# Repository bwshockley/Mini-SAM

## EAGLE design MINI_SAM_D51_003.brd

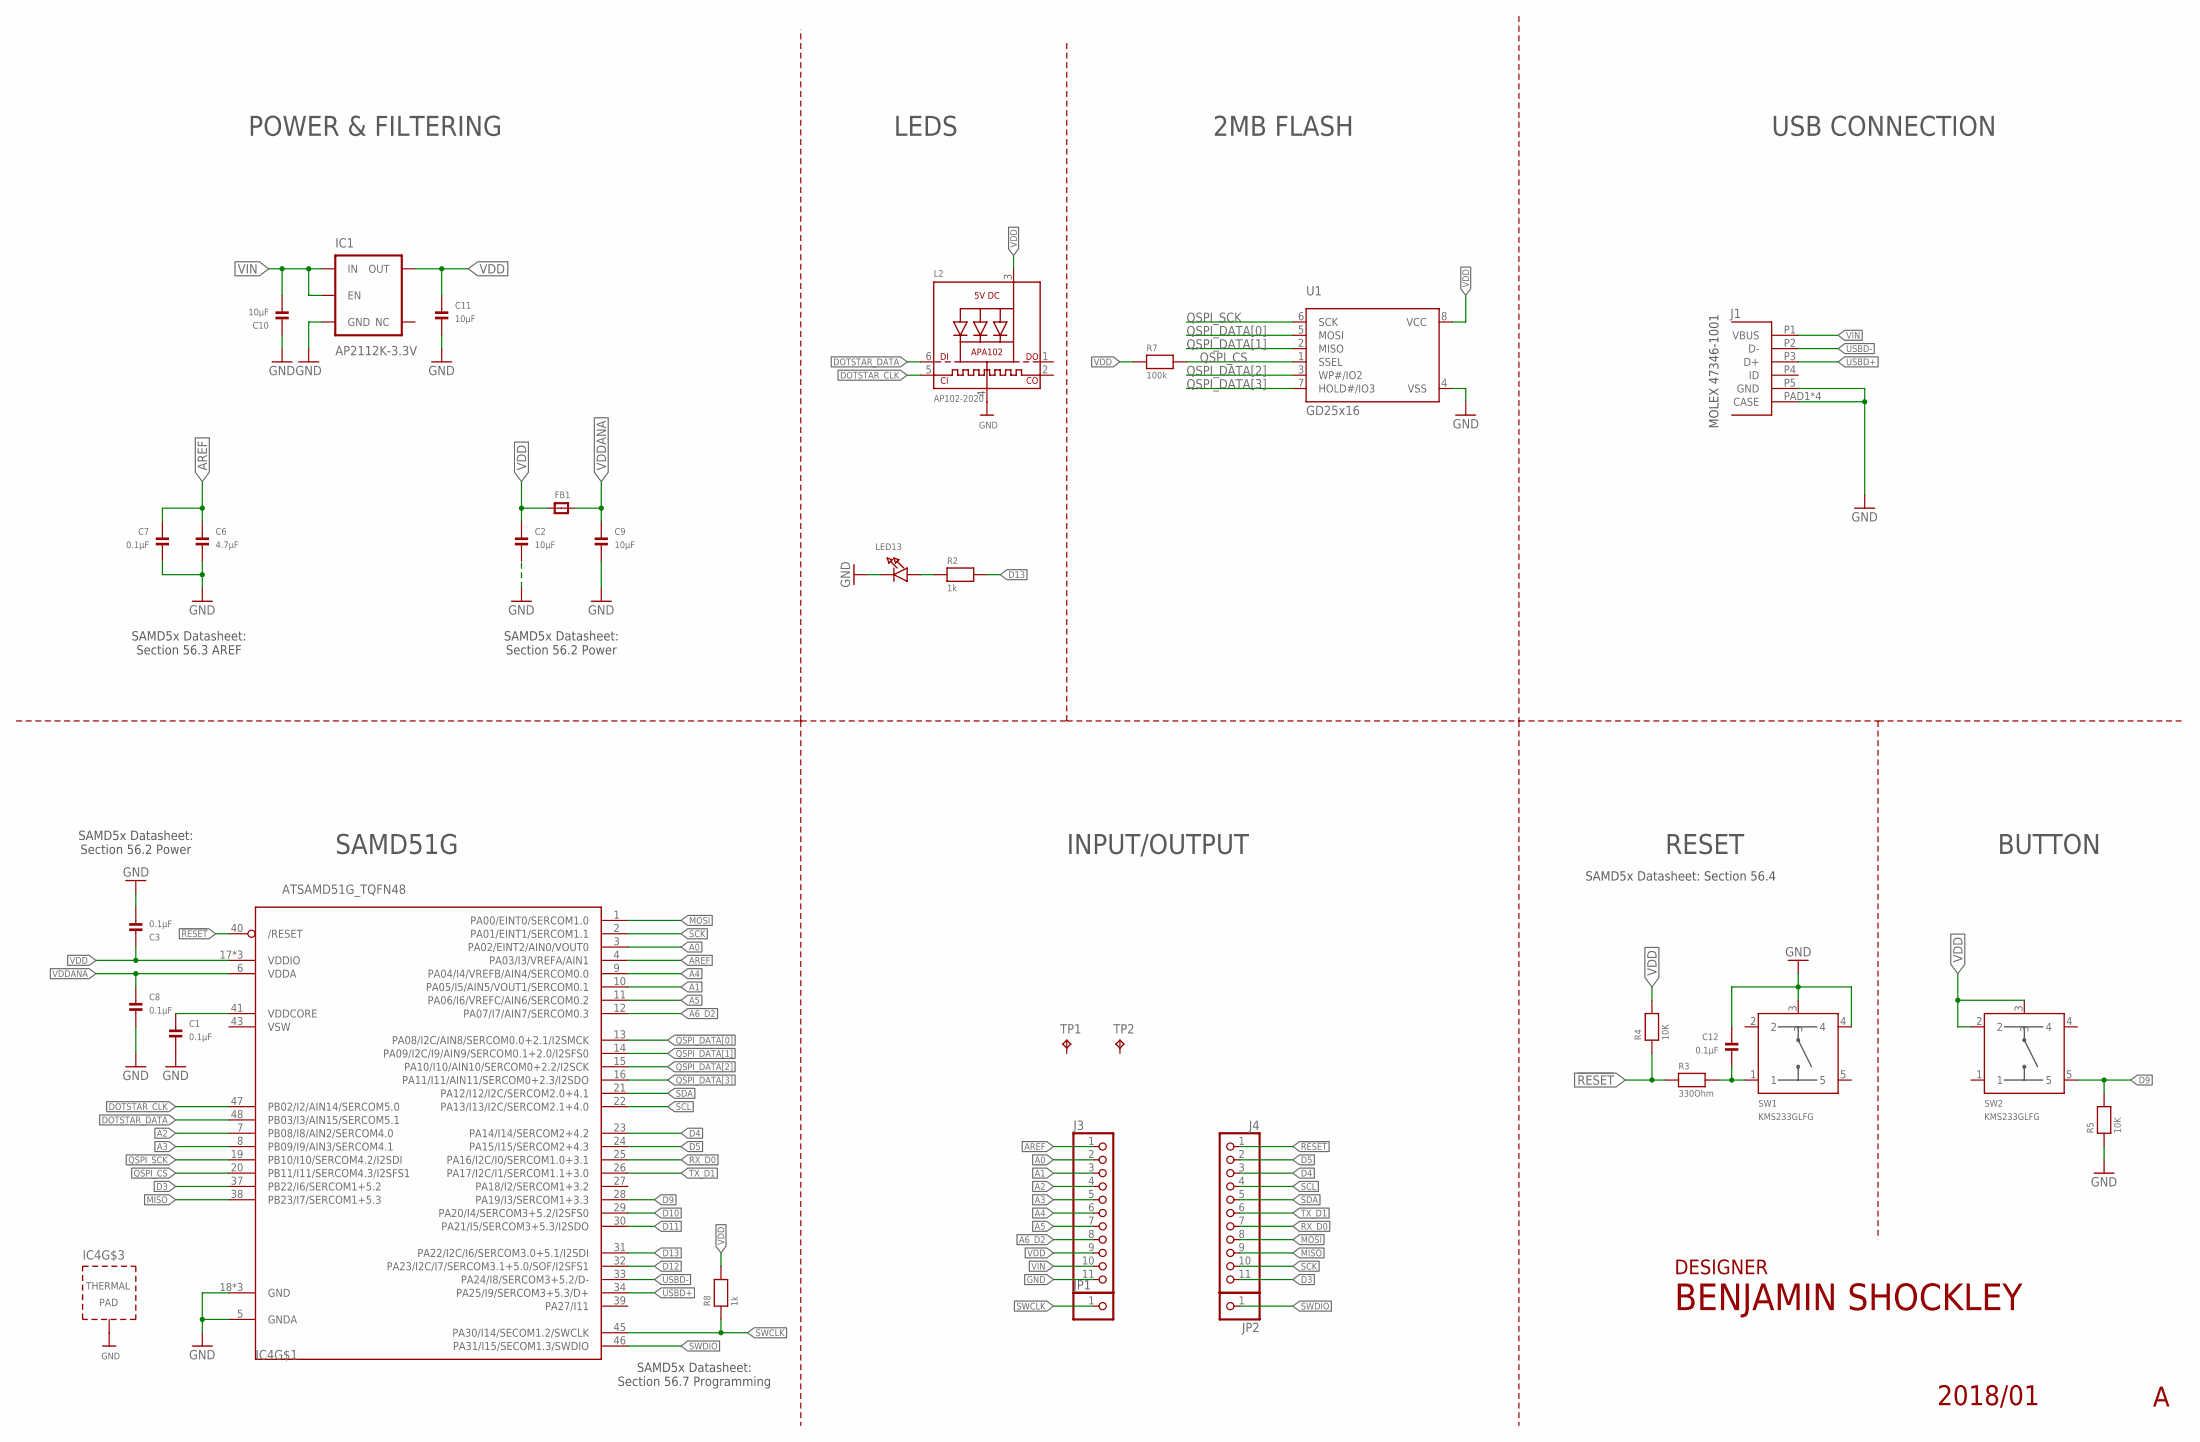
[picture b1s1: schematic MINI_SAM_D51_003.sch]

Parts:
C1, C3, C7, C8, C12: 0.1µF; _0603MP
C2, C9, C10, C11: 10µF; _0603MP
C6: 4.7µF; _0603MP
FB1: FERRITE_0603MP; _0603MP
IC1: AP2112K-3.3V; SOT23-5
IC4: ATSAMD51G_TQFN48; TQFN48_7MM
J1: MOLEX_47346-100147346; MOLEX_47346-1001
J3, J4: PINHD-1X111X11_SMT; 1X11_SMT
JP1, JP2: HEADER-1X1ROUND; 1X01_ROUND
L2: AP102-2020; APA102_2020
LED13: LED0603_NOOUTLINE; CHIPLED_0603_NOOUTLINE
R2, R8: 1k; _0603MP
R3: 330Ohm; _0603MP
R4, R5: 10K; _0603MP
R7: 100k; _0603MP
SW1, SW2: KMS233GLFG; KMS_SWITCH
TP1, TP2: TPB1,27; B1,27
U1: GD25x16; USON8

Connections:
!RESET: IC4.40 (/RESET), J4.1, R3.1, R4.1
A0: IC4.3 (PA02/EINT2/AIN0/VOUT0), J3.2
A1: IC4.10 (PA05/I5/AIN5/VOUT1/SERCOM0.1), J3.3
A2: IC4.7 (PB08/I8/AIN2/SERCOM4.0), J3.4
A3: IC4.8 (PB09/I9/AIN3/SERCOM4.1), J3.5
A4: IC4.9 (PA04/I4/VREFB/AIN4/SERCOM0.0), J3.6
A5: IC4.11 (PA06/I6/VREFC/AIN6/SERCOM0.2), J3.7
A6_D2: IC4.12 (PA07/I7/AIN7/SERCOM0.3), J3.8
AREF: C6.1, C7.1, IC4.4 (PA03/I3/VREFA/AIN1), J3.1
D3: IC4.37 (PB22/I6/SERCOM1+5.2), J4.11
D4: IC4.23 (PA14/I14/SERCOM2+4.2), J4.3
D5: IC4.24 (PA15/I15/SERCOM2+4.3), J4.2
D9: IC4.28 (PA19/I3/SERCOM1+3.3), R5.2, SW2.5
D10: IC4.29 (PA20/I4/SERCOM3+5.2/I2SFS0)
D11: IC4.30 (PA21/I5/SERCOM3+5.3/I2SDO)
D12: IC4.32 (PA23/I2C/I7/SERCOM3.1+5.0/SOF/I2SFS1)
D13: IC4.31 (PA22/I2C/I6/SERCOM3.0+5.1/I2SDI), R2.2
DOTSTAR_CLK: IC4.47 (PB02/I2/AIN14/SERCOM5.0), L2.5 (CKI)
DOTSTAR_DATA: IC4.48 (PB03/I3/AIN15/SERCOM5.1), L2.6 (DI)
GND: C1.2, C2.2, C3.2, C6.2, C7.2, C8.2, C9.2, C10.1, C11.2, C12.1, IC1.2 (GND), IC4.5 (GNDA), IC4.18 (GND), IC4.35 (GND), IC4.42 (GND), IC4.THERMAL (TP), J1.P5 (GND), J1.PAD1 (CASE), J1.PAD2 (CASE), J1.PAD3 (CASE), J1.PAD4 (CASE), J3.11, L2.4 (GND), LED13.C, R5.1, SW1.3, SW1.4, U1.4 (VSS)
MISO: IC4.38 (PB23/I7/SERCOM1+5.3), J4.9
MOSI: IC4.1 (PA00/EINT0/SERCOM1.0), J4.8
unnamed: LED13.A, R2.1
unnamed: C12.2, R3.2, SW1.1
unnamed: C1.1, IC4.41 (VDDCORE)
QSPI_CS: IC4.20 (PB11/I11/SERCOM4.3/I2SFS1), R7.2, U1.1 (SSEL)
QSPI_DATA[0]: IC4.13 (PA08/I2C/AIN8/SERCOM0.0+2.1/I2SMCK), U1.5 (MOSI)
QSPI_DATA[1]: IC4.14 (PA09/I2C/I9/AIN9/SERCOM0.1+2.0/I2SFS0), U1.2 (MISO)
QSPI_DATA[2]: IC4.15 (PA10/I10/AIN10/SERCOM0+2.2/I2SCK), U1.3 (WP#/IO2)
QSPI_DATA[3]: IC4.16 (PA11/I11/AIN11/SERCOM0+2.3/I2SDO), U1.7 (HOLD#/IO3)
QSPI_SCK: IC4.19 (PB10/I10/SERCOM4.2/I2SDI), U1.6 (SCK)
RX_D0: IC4.25 (PA16/I2C/I0/SERCOM1.0+3.1), J4.7
SCK: IC4.2 (PA01/EINT1/SERCOM1.1), J4.10
SCL: IC4.22 (PA13/I13/I2C/SERCOM2.1+4.0), J4.4
SDA: IC4.21 (PA12/I12/I2C/SERCOM2.0+4.1), J4.5
SWCLK: IC4.45 (PA30/I14/SECOM1.2/SWCLK), JP1.1, R8.1
SWDIO: IC4.46 (PA31/I15/SECOM1.3/SWDIO), JP2.1
TX_D1: IC4.26 (PA17/I2C/I1/SERCOM1.1+3.0), J4.6
USBD+: IC4.34 (PA25/I9/SERCOM3+5.3/D+), J1.P3 (D+)
USBD-: IC4.33 (PA24/I8/SERCOM3+5.2/D-), J1.P2 (D-)
VDD: C2.1, C3.1, C11.1, FB1.1, IC1.5 (OUT), IC4.17 (VDDIO), IC4.36 (VDDIO), IC4.44 (VDDIO), J3.9, L2.3 (VDD), R4.2, R7.1, R8.2, SW2.2, SW2.3, U1.8 (VCC)
VDDANA: C8.1, C9.1, FB1.2, IC4.6 (VDDA)
VIN: C10.2, IC1.1 (IN), IC1.3 (EN), J1.P1 (VBUS), J3.10
VSW: IC4.43 (VSW)

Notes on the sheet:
INPUT/OUTPUT
RESET
POWER & FILTERING
SAMD51G
LEDS
USB CONNECTION
MOLEX 47346-1001
BUTTON
DESIGNER
SAMD5x Datasheet: Section 56.4
2MB FLASH
SAMD5x Datasheet: Section 56.3 AREF
SAMD5x Datasheet: Section 56.2 Power
SAMD5x Datasheet: Section 56.7 Programming

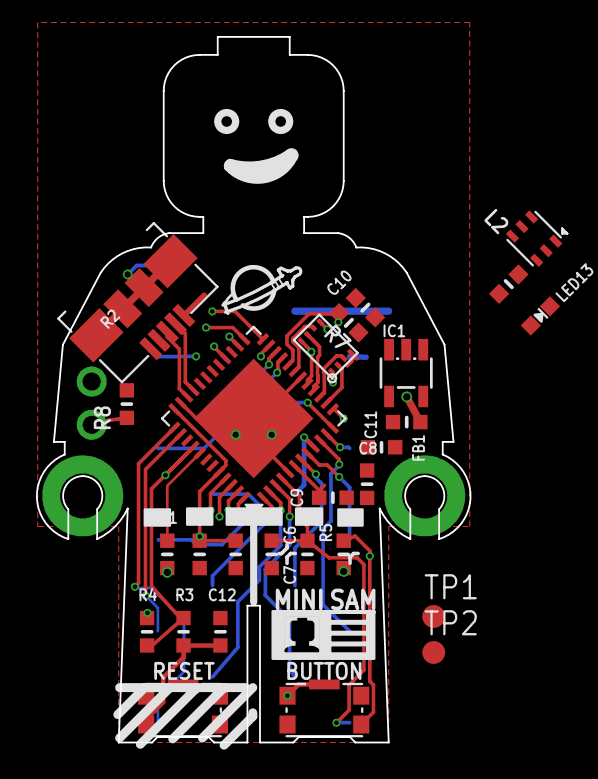
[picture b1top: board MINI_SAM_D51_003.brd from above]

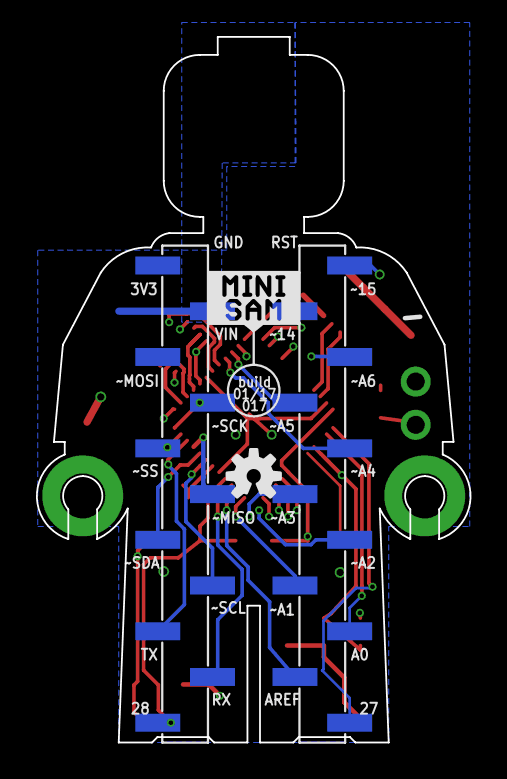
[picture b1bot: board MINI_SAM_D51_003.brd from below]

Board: 4 copper layers, 24.1 x 39.2 mm, 32 parts (3 on the bottom side), 40 nets.

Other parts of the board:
U$3: OSHW-LOGO-S

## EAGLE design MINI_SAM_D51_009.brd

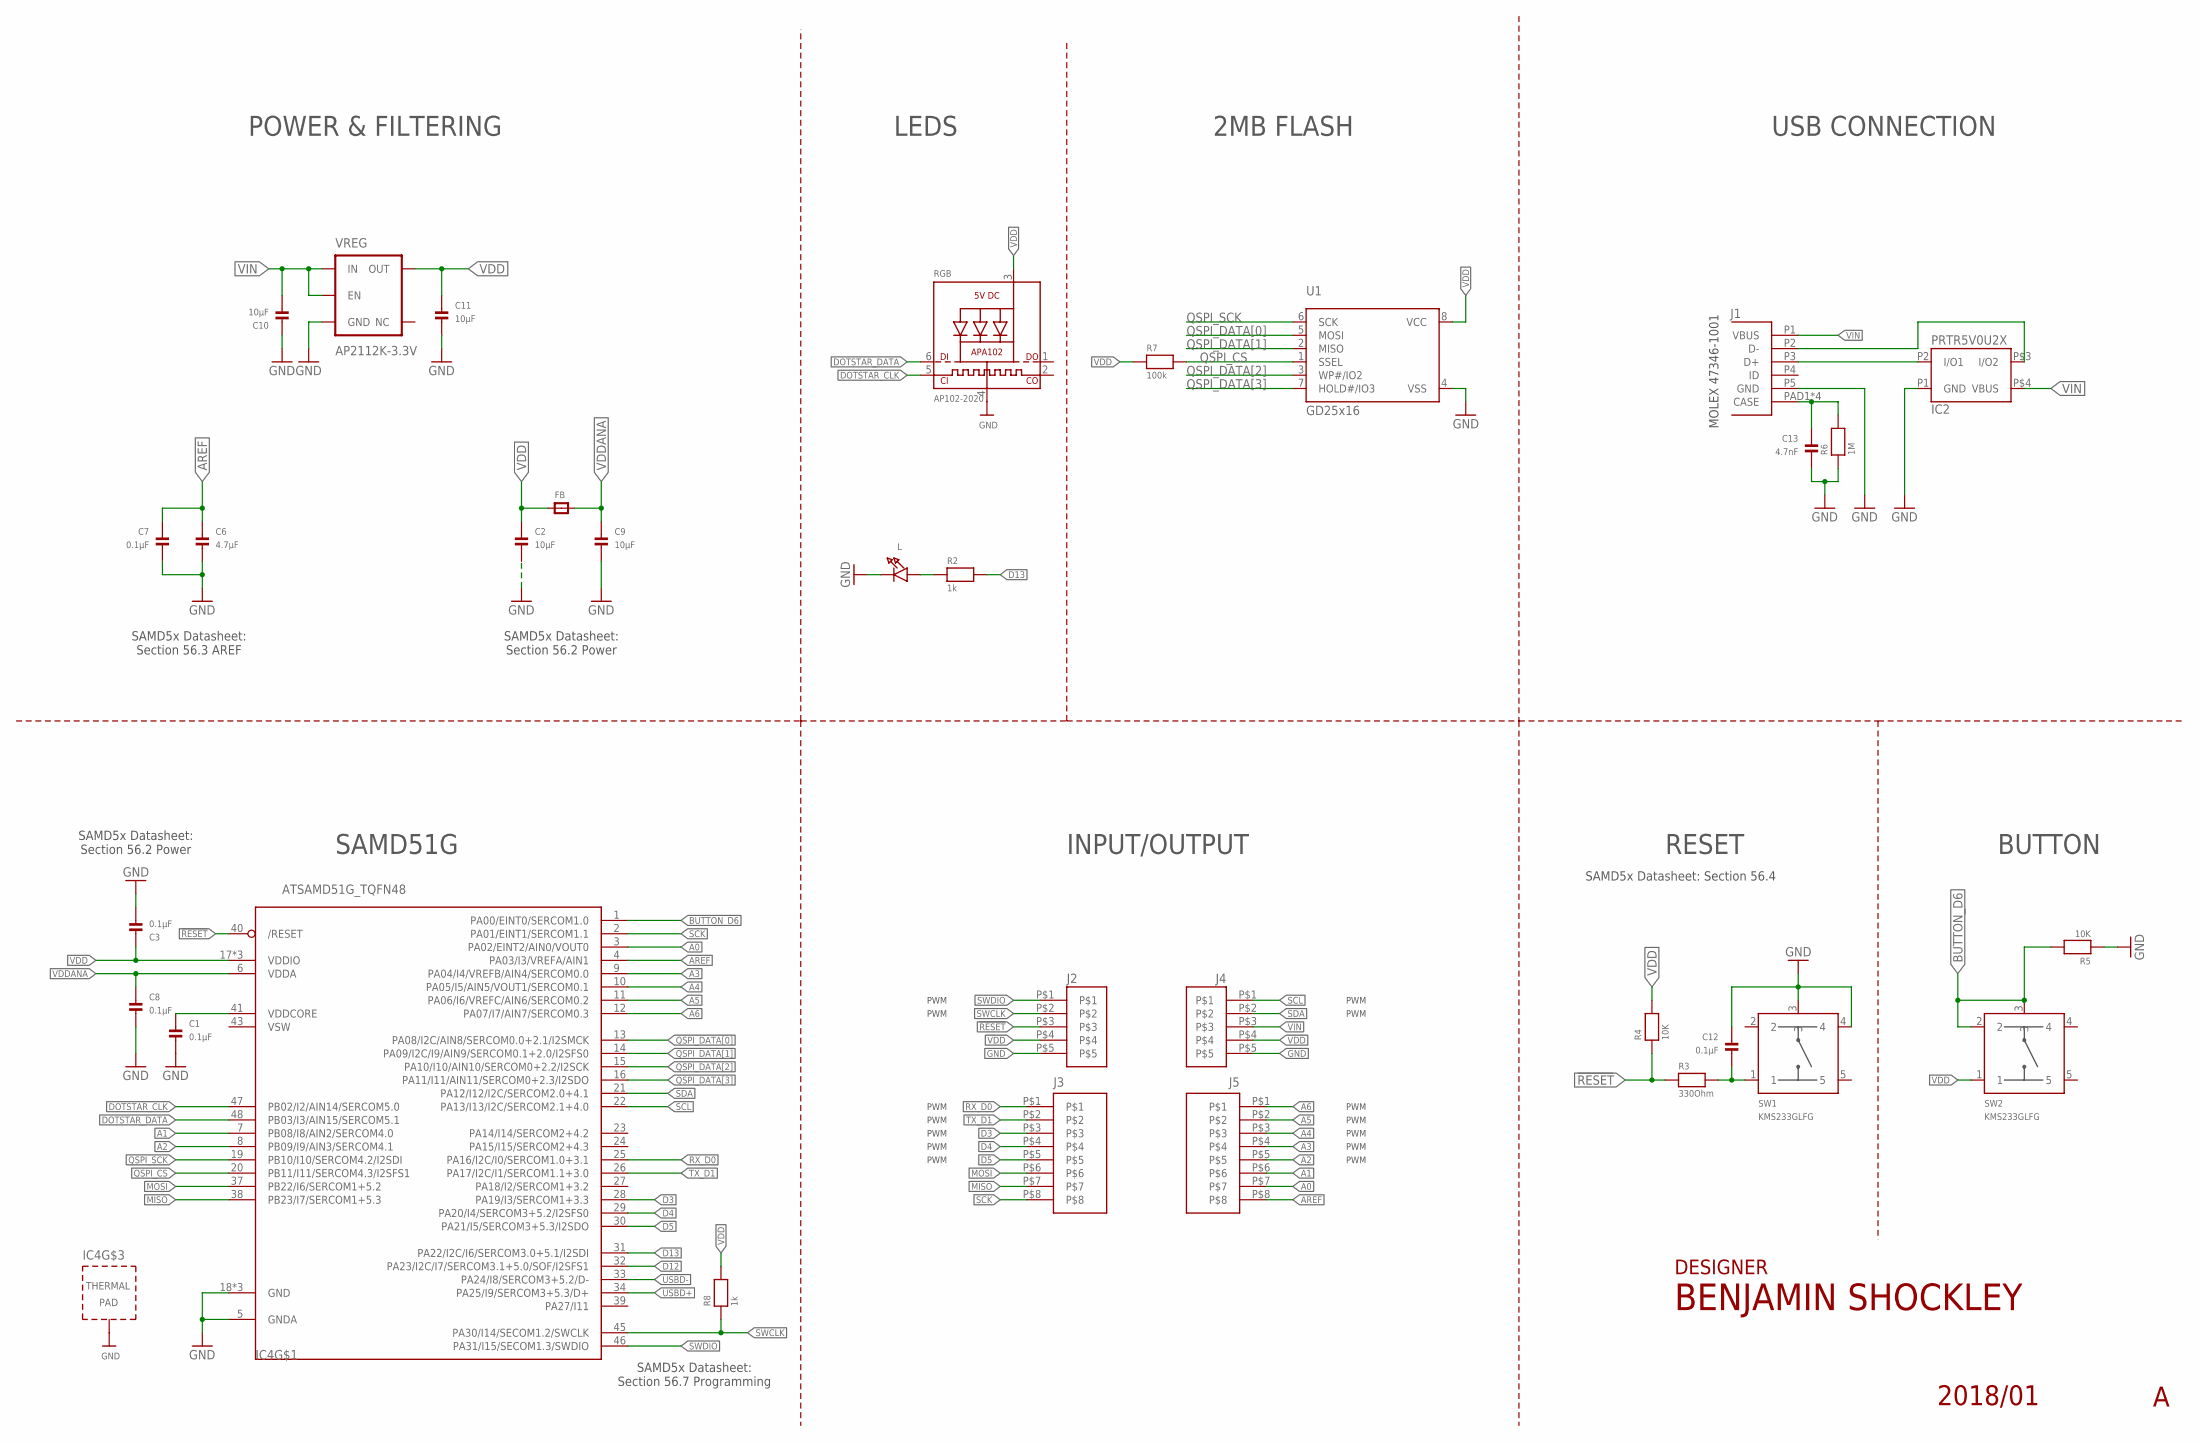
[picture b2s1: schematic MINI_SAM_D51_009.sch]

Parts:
C1, C3, C7, C8, C12: 0.1µF; _0603MP
C2, C9, C10, C11: 10µF; _0603MP
C6: 4.7µF; _0603MP
C13: 4.7nF; _0603MP
FB: FERRITE_0603MP; _0603MP
IC2: PRTR5V0U2X; SOT143B_REFLOW
IC4: ATSAMD51G_TQFN48; TQFN48_7MM
J1: MOLEX_47346-100147346; MOLEX_47346-1001
J2, J4: 1X5_HEADER_1.27MM
J3, J5: 1X8_HEADER_1.27MM
L: LED0603_NOOUTLINE; CHIPLED_0603_NOOUTLINE
R2, R8: 1k; _0603MP
R3: 330Ohm; _0603MP
R4, R5: 10K; _0603MP
R6: 1M; _0603MP
R7: 100k; _0603MP
RGB: AP102-2020; APA102_2020
SW1, SW2: KMS233GLFG; KMS_SWITCH
U1: GD25x16; USON8
VREG: AP2112K-3.3V; SOT23-5

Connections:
!RESET: IC4.40 (/RESET), J2.P$3, R3.1, R4.1
A0: IC4.3 (PA02/EINT2/AIN0/VOUT0), J5.P$7
A1: IC4.7 (PB08/I8/AIN2/SERCOM4.0), J5.P$6
A2: IC4.8 (PB09/I9/AIN3/SERCOM4.1), J5.P$5
A3: IC4.9 (PA04/I4/VREFB/AIN4/SERCOM0.0), J5.P$4
A4: IC4.10 (PA05/I5/AIN5/VOUT1/SERCOM0.1), J5.P$3
A5: IC4.11 (PA06/I6/VREFC/AIN6/SERCOM0.2), J5.P$2
A6: IC4.12 (PA07/I7/AIN7/SERCOM0.3), J5.P$1
AREF: C6.1, C7.1, IC4.4 (PA03/I3/VREFA/AIN1), J5.P$8
BUTTON_D6: IC4.1 (PA00/EINT0/SERCOM1.0), R5.2, SW2.2, SW2.3
D3: IC4.28 (PA19/I3/SERCOM1+3.3), J3.P$3
D4: IC4.29 (PA20/I4/SERCOM3+5.2/I2SFS0), J3.P$4
D5: IC4.30 (PA21/I5/SERCOM3+5.3/I2SDO), J3.P$5
D12: IC4.32 (PA23/I2C/I7/SERCOM3.1+5.0/SOF/I2SFS1)
D13: IC4.31 (PA22/I2C/I6/SERCOM3.0+5.1/I2SDI), R2.2
DOTSTAR_CLK: IC4.47 (PB02/I2/AIN14/SERCOM5.0), RGB.5 (CKI)
DOTSTAR_DATA: IC4.48 (PB03/I3/AIN15/SERCOM5.1), RGB.6 (DI)
GND: C1.2, C2.2, C3.2, C6.2, C7.2, C8.2, C9.2, C10.1, C11.2, C12.1, C13.2, IC2.P1 (GND), IC4.5 (GNDA), IC4.18 (GND), IC4.35 (GND), IC4.42 (GND), IC4.THERMAL (TP), J1.P5 (GND), J2.P$5, J4.P$5, L.C, R5.1, R6.1, RGB.4 (GND), SW1.3, SW1.4, U1.4 (VSS), VREG.2 (GND)
MISO: IC4.38 (PB23/I7/SERCOM1+5.3), J3.P$7
MOSI: IC4.37 (PB22/I6/SERCOM1+5.2), J3.P$6
unnamed: C13.1, J1.PAD1 (CASE), J1.PAD2 (CASE), J1.PAD3 (CASE), J1.PAD4 (CASE), R6.2
unnamed: L.A, R2.1
unnamed: C12.2, R3.2, SW1.1
unnamed: C1.1, IC4.41 (VDDCORE)
QSPI_CS: IC4.20 (PB11/I11/SERCOM4.3/I2SFS1), R7.2, U1.1 (SSEL)
QSPI_DATA[0]: IC4.13 (PA08/I2C/AIN8/SERCOM0.0+2.1/I2SMCK), U1.5 (MOSI)
QSPI_DATA[1]: IC4.14 (PA09/I2C/I9/AIN9/SERCOM0.1+2.0/I2SFS0), U1.2 (MISO)
QSPI_DATA[2]: IC4.15 (PA10/I10/AIN10/SERCOM0+2.2/I2SCK), U1.3 (WP#/IO2)
QSPI_DATA[3]: IC4.16 (PA11/I11/AIN11/SERCOM0+2.3/I2SDO), U1.7 (HOLD#/IO3)
QSPI_SCK: IC4.19 (PB10/I10/SERCOM4.2/I2SDI), U1.6 (SCK)
RX_D0: IC4.25 (PA16/I2C/I0/SERCOM1.0+3.1), J3.P$1
SCK: IC4.2 (PA01/EINT1/SERCOM1.1), J3.P$8
SCL: IC4.22 (PA13/I13/I2C/SERCOM2.1+4.0), J4.P$1
SDA: IC4.21 (PA12/I12/I2C/SERCOM2.0+4.1), J4.P$2
SWCLK: IC4.45 (PA30/I14/SECOM1.2/SWCLK), J2.P$2, R8.1
SWDIO: IC4.46 (PA31/I15/SECOM1.3/SWDIO), J2.P$1
TX_D1: IC4.26 (PA17/I2C/I1/SERCOM1.1+3.0), J3.P$2
USBD+: IC2.P2 (I/O1), IC4.34 (PA25/I9/SERCOM3+5.3/D+), J1.P3 (D+)
USBD-: IC2.P$3 (I/O2), IC4.33 (PA24/I8/SERCOM3+5.2/D-), J1.P2 (D-)
VDD: C2.1, C3.1, C11.1, FB.1, IC4.17 (VDDIO), IC4.36 (VDDIO), IC4.44 (VDDIO), J2.P$4, J4.P$4, R4.2, R7.1, R8.2, RGB.3 (VDD), SW2.1, U1.8 (VCC), VREG.5 (OUT)
VDDANA: C8.1, C9.1, FB.2, IC4.6 (VDDA)
VIN: C10.2, IC2.P$4 (VBUS), J1.P1 (VBUS), J4.P$3, VREG.1 (IN), VREG.3 (EN)
VSW: IC4.43 (VSW)

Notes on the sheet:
INPUT/OUTPUT
RESET
POWER & FILTERING
SAMD51G
LEDS
USB CONNECTION
MOLEX 47346-1001
BUTTON
DESIGNER
SAMD5x Datasheet: Section 56.4
2MB FLASH
SAMD5x Datasheet: Section 56.3 AREF
SAMD5x Datasheet: Section 56.2 Power
SAMD5x Datasheet: Section 56.7 Programming
PWM

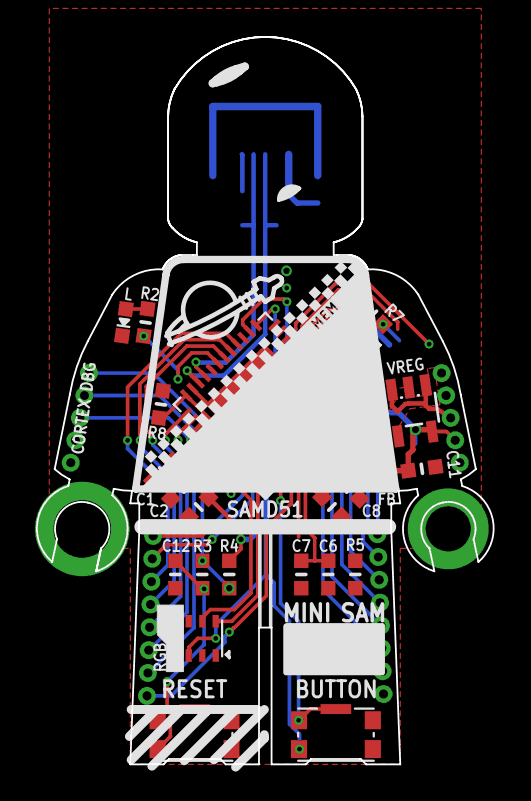
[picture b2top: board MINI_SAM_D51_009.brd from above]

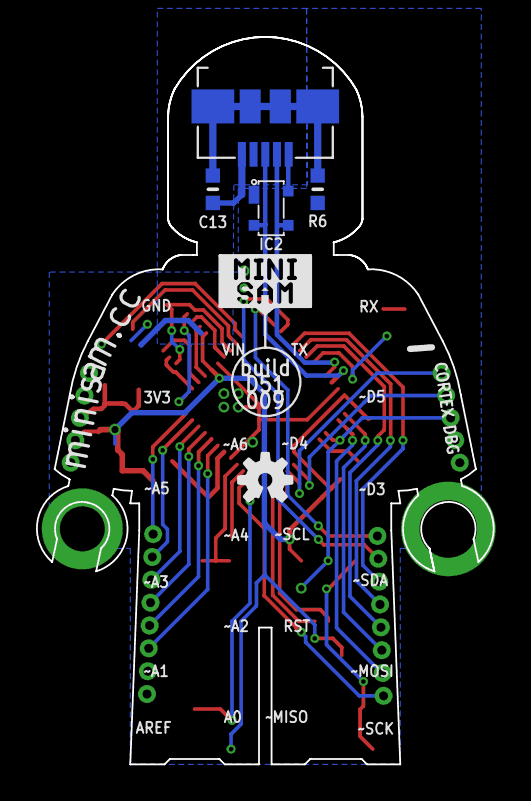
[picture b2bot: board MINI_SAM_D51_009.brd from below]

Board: 2 copper layers, 25.4 x 40.4 mm, 33 parts (5 on the bottom side), 41 nets.

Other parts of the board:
U$3: OSHW-LOGO-S

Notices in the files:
parts and their libraries:
microbuilder: This work is placed in the public domain, and may be freely used for commercial and non-commercial work with the following conditions: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
SparkFun-Aesthetics: Licensing: Creative Commons ShareAlike 4.0 International - https://creativecommons.org/licenses/by-sa/4.0
